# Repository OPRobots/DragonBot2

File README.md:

# DragonBot2

Robot **siguelíneas tipo Robotracer** de alto rendimiento para competir en la **All Japan Robotracer 2027**. Basado en un **STM32F405 @168 MHz**, con **24 sensores de línea** multiplexados, **tracción tetra** con 4 motores coreless, encoders magnéticos de alta resolución, **succión** y un **EKF de odometría** de 6 estados, todo con registro de datos a bordo y herramientas de análisis offline.

## 🎯 Objetivo

Desarrollar un robotracer competitivo para la **All Japan Robotracer 2027**. El firmware contempla tres modos de competición:

- **Linefollower**
- **Robotracer**
- **Drag race**

## 🏆 Palmarés

Todavía en desarrollo — **sin resultados de competición por el momento**.

| 🥇 | 🥈 | 🥉 |
| --- | --- | --- |
| **0** | **0** | **0** |

### Resultados por Evento

| Evento | Categoría | Posición | Año |
| --- | --- | --- | --- |
| _Pendiente_ | — | — | — |

---

## ⚙️ Hardware

- **Microcontrolador**: STM32F405RGT6 @168 MHz (LQFP-64)
- **Driver de motores**: 2× MP6615 (puente H con sensado de corriente bidireccional integrado)
- **IMU**: LSM6DSR (giroscopio, 1000/2000/4000 dps)
- **Encoders**: 2× AS5145B-HSST magnéticos de 12 bits (leídos en cuadratura ×4 por hardware → 4096 cuentas/vuelta)
- **Sensores de línea**: 24× ITR8307 (reflectivos) leídos a través de 3× multiplexores CD4051B
- **Sensores de marca**: 4× ITR8307 (laterales, para *landmarks* del robotracer)
- **Sensor de presión**: BMP280
- **Memoria externa**: SRAM SPI 23AA04M-I/ST de 512 KB + EEPROM en la flash interna del MCU
- **Receptor infrarrojo**: TSSP77038TR (38 kHz, mando RC5)
- **Regulador**: DC-DC conmutado CN3903 + LDO
- **Mosfet de succión**: BUK9Q20-40H
- **LEDs**: 1× LED RGB 5050, 10 LEDs de información, 1 LED de estado
- **Batería**: LiPo 3S (11,1–12,6 V), fabricada a partir de 3 celdas 1S de 300 mAh; conector JST-XH de 4 pines
- **Conectores de motores**: Hirose DF13 a 1,25 mm
- **Interfaz**: USB-C (ST-Link + USART3)

### Tracción

- **Tracción tetra**: 2 ruedas por lado, con **4 motores coreless de 7.4v** (2 por lado)
- **Reducción**: piñón de 8 dientes → engranaje de 40 dientes (**5:1**)
- **Ruedas**: Ø≈23 mm, con llanta impresa en PLA, una capa de espuma gruesa y una lámina de silicona exterior de gran adherencia
- **Succión**: doble ventilador centrífugo para aumentar el agarre a alta velocidad, usando **2 motores coreless de 7.4v**

### PCBs

El repositorio incluye dos placas diseñadas en KiCad (proyecto, gerbers y BOM):

- **Main**: MCU, drivers, sensores, encoders, memoria y regulación.
- **Chasis**: placa de chasis con pads de interconexión y switch de alimentación.

### Pinout (resumen)

| Función | Periférico / Pin |
| --- | --- |
| PWM motores | TIM1 CH1–CH4 (PA8–PA11) |
| Encoders | TIM3 (PB4/PB5), TIM4 (PB6/PB7) |
| Succión / RGB | TIM8 CH1–CH4 (PC6–PC9) |
| Sensores de línea | ADC1 IN10–IN12 (PC0–PC2) + selección de mux (PC13–PC15) |
| Sensores de marca / corriente de motor | ADC2 IN0–IN5 (PA0–PA5) |
| Tensión de batería | ADC2 IN13 (PC3) |
| IMU / BMP280 / SRAM | SPI3 (PC10–PC12) |
| Mando IR 38 kHz | EXTI12 (PA12) |
| Serie / ST-Link | USART3 (PB10/PB11) |

## 💻 Software

- Programado en **VSCode + PlatformIO** con **libopencm3**. Flasheo y depuración por **ST-Link**.
- **Scheduler** con **SysTick a 8 kHz** repartido en 8 slots → cada tarea corre a **1 kHz**.
- Todas las señales analógicas se leen por **DMA** (ADC1 y ADC2).
- Los **sensores de línea** se leen a través de los 3 multiplexores; la posición sobre la línea (rango ±1000) se calcula por media ponderada, con filtro de ventana **Bigger Filtro** y **detección automática del color de la línea** (blanca/negra).
- Los **encoders** se leen en **cuadratura por hardware** (TIM3/TIM4), con resolución de overflow por máxima verosimilitud.
- La **IMU** se lee por SPI con *data-ready*; el LSM6DSR se configura a ODR 833 Hz **sin filtro hardware** (medida cruda para el estimador).
- **Odometría con EKF de 6 estados** `[x, y, θ, v, ω, bias_gyro]`, con `dt` real medido por DWT, **ZUPT** y **detección de derrape**.
- **Lazo de control a 1 kHz** con PID de velocidad lineal y PID de posición de línea (angular) que reparte la tensión entre las ruedas, con **compensación de la tensión de batería**.
- **Estrategias de velocidad**: `SPEED_TEST`, `SPEED_NORMAL`, `SPEED_MEDIUM`, `SPEED_FAST`, `SPEED_SUPER` y `SPEED_HAKI` (2000–4000 mm/s), con ganancias escaladas ∝ 1/v.
- **Menú** de configuración y de *run* por LEDs, manejable con botones y con **mando RC5**; los parámetros se persisten en EEPROM.
- **Calibraciones**: offset del giroscopio, sensores, separación de ruedas (girando 2π con el gyro), escala de rueda (distancia patrón) y escalón de rotación (test T1).
- **Registro a bordo**: log en la **SRAM SPI de 512 KB** (ring en RAM + volcado diferido en los slots del SysTick), volcado por serie para análisis offline.

### Herramientas de análisis (`source_code/tools/`)

- `line_control_tuner.py` — métricas y predicción de ganancias del lazo de línea.
- `linear_speed_analyzer.py` — análisis del lazo de velocidad lineal y *feedforward*.
- `parse_odometry_log.py` — parseo y gráficas del log de odometría.

### Documentación técnica interna (`.features/`)

- `odometry/ROADMAP.md` — odometría y EKF.
- `pid_tuning/ROADMAP.md` — tuning del control de velocidad y de línea.
- `linear_speed/linear_speed_analysis_and_plan.md` — análisis del lazo lineal.

## 🎥 Vídeos

https://github.com/user-attachments/assets/3e48b05f-021b-4ee5-92f5-90e260f31eb7

## 📄 Licencia

Distribuido bajo la **PolyForm Noncommercial License 1.0.0**. Ver [LICENSE](LICENSE).

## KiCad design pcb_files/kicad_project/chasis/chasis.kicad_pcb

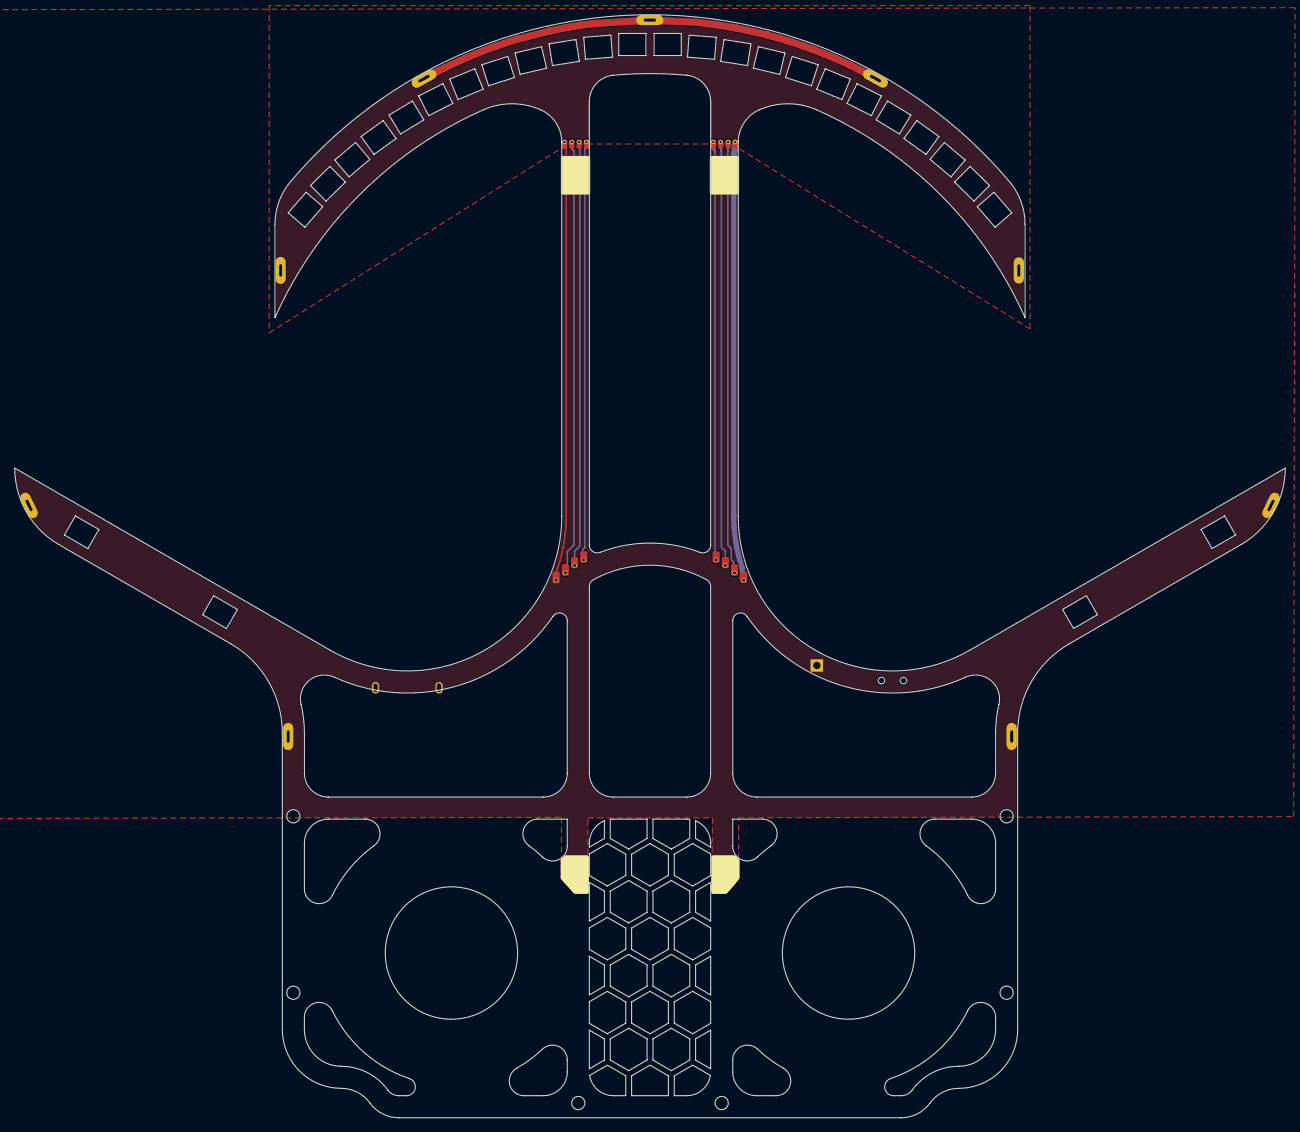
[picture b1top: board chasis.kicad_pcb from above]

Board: 2 copper layers, 172.8 x 150.0 mm, 6 parts (1 on the bottom side), 8 nets.

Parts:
J1: Conn_01x08_Pin; DragonBot_pads_main
J2: Conn_01x08_Pin; DragonBot_pads_morro
J3: Conn_01x01_Pin; PinHeader_1x01_P2.54mm_Vertical
JP2: SolderJumper_2_Open; SolderJumper-2_P1.3mm_Open_RoundedPad1.0x1.5mm
POWER_SWITCH1: SW_DPDT_x2; Generic_Swich_ONOFF
USB1: USB-C ST-Link USART

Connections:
GND: J1.1, J2.1, J3.1 (Pin_1_1), USB1.13 (SHIELD)
unnamed: J1.2, J2.2
unnamed: J1.3, J2.3
unnamed: J1.4, J2.4
unnamed: J1.5, J2.5
unnamed: J1.6, J2.6
unnamed: J1.7, J2.7
unnamed: J1.8, J2.8

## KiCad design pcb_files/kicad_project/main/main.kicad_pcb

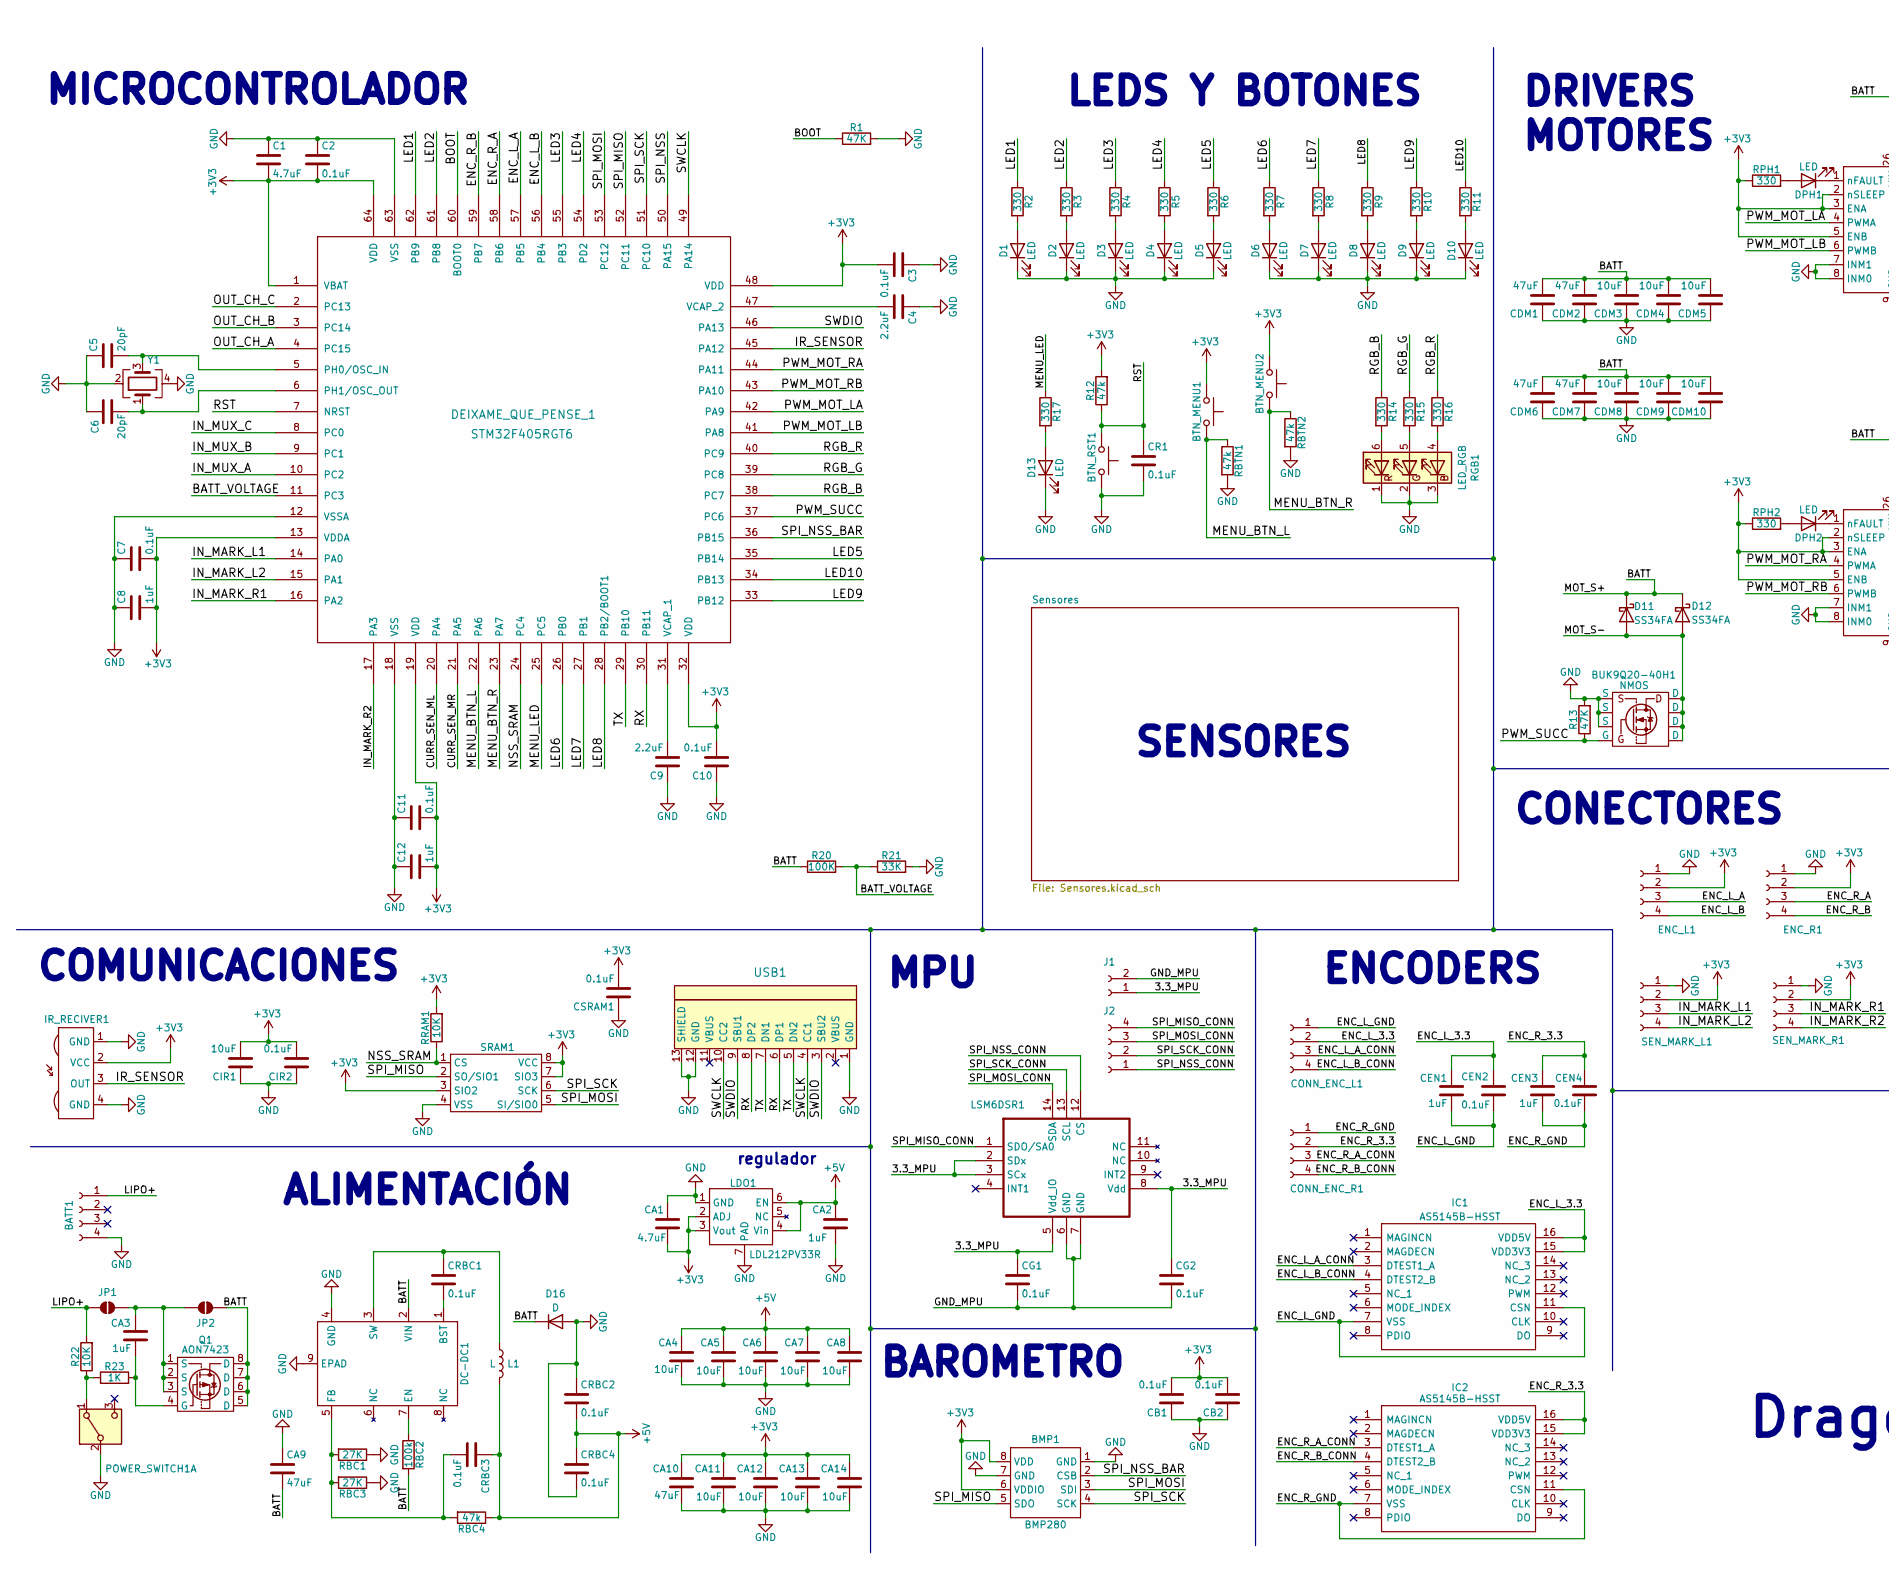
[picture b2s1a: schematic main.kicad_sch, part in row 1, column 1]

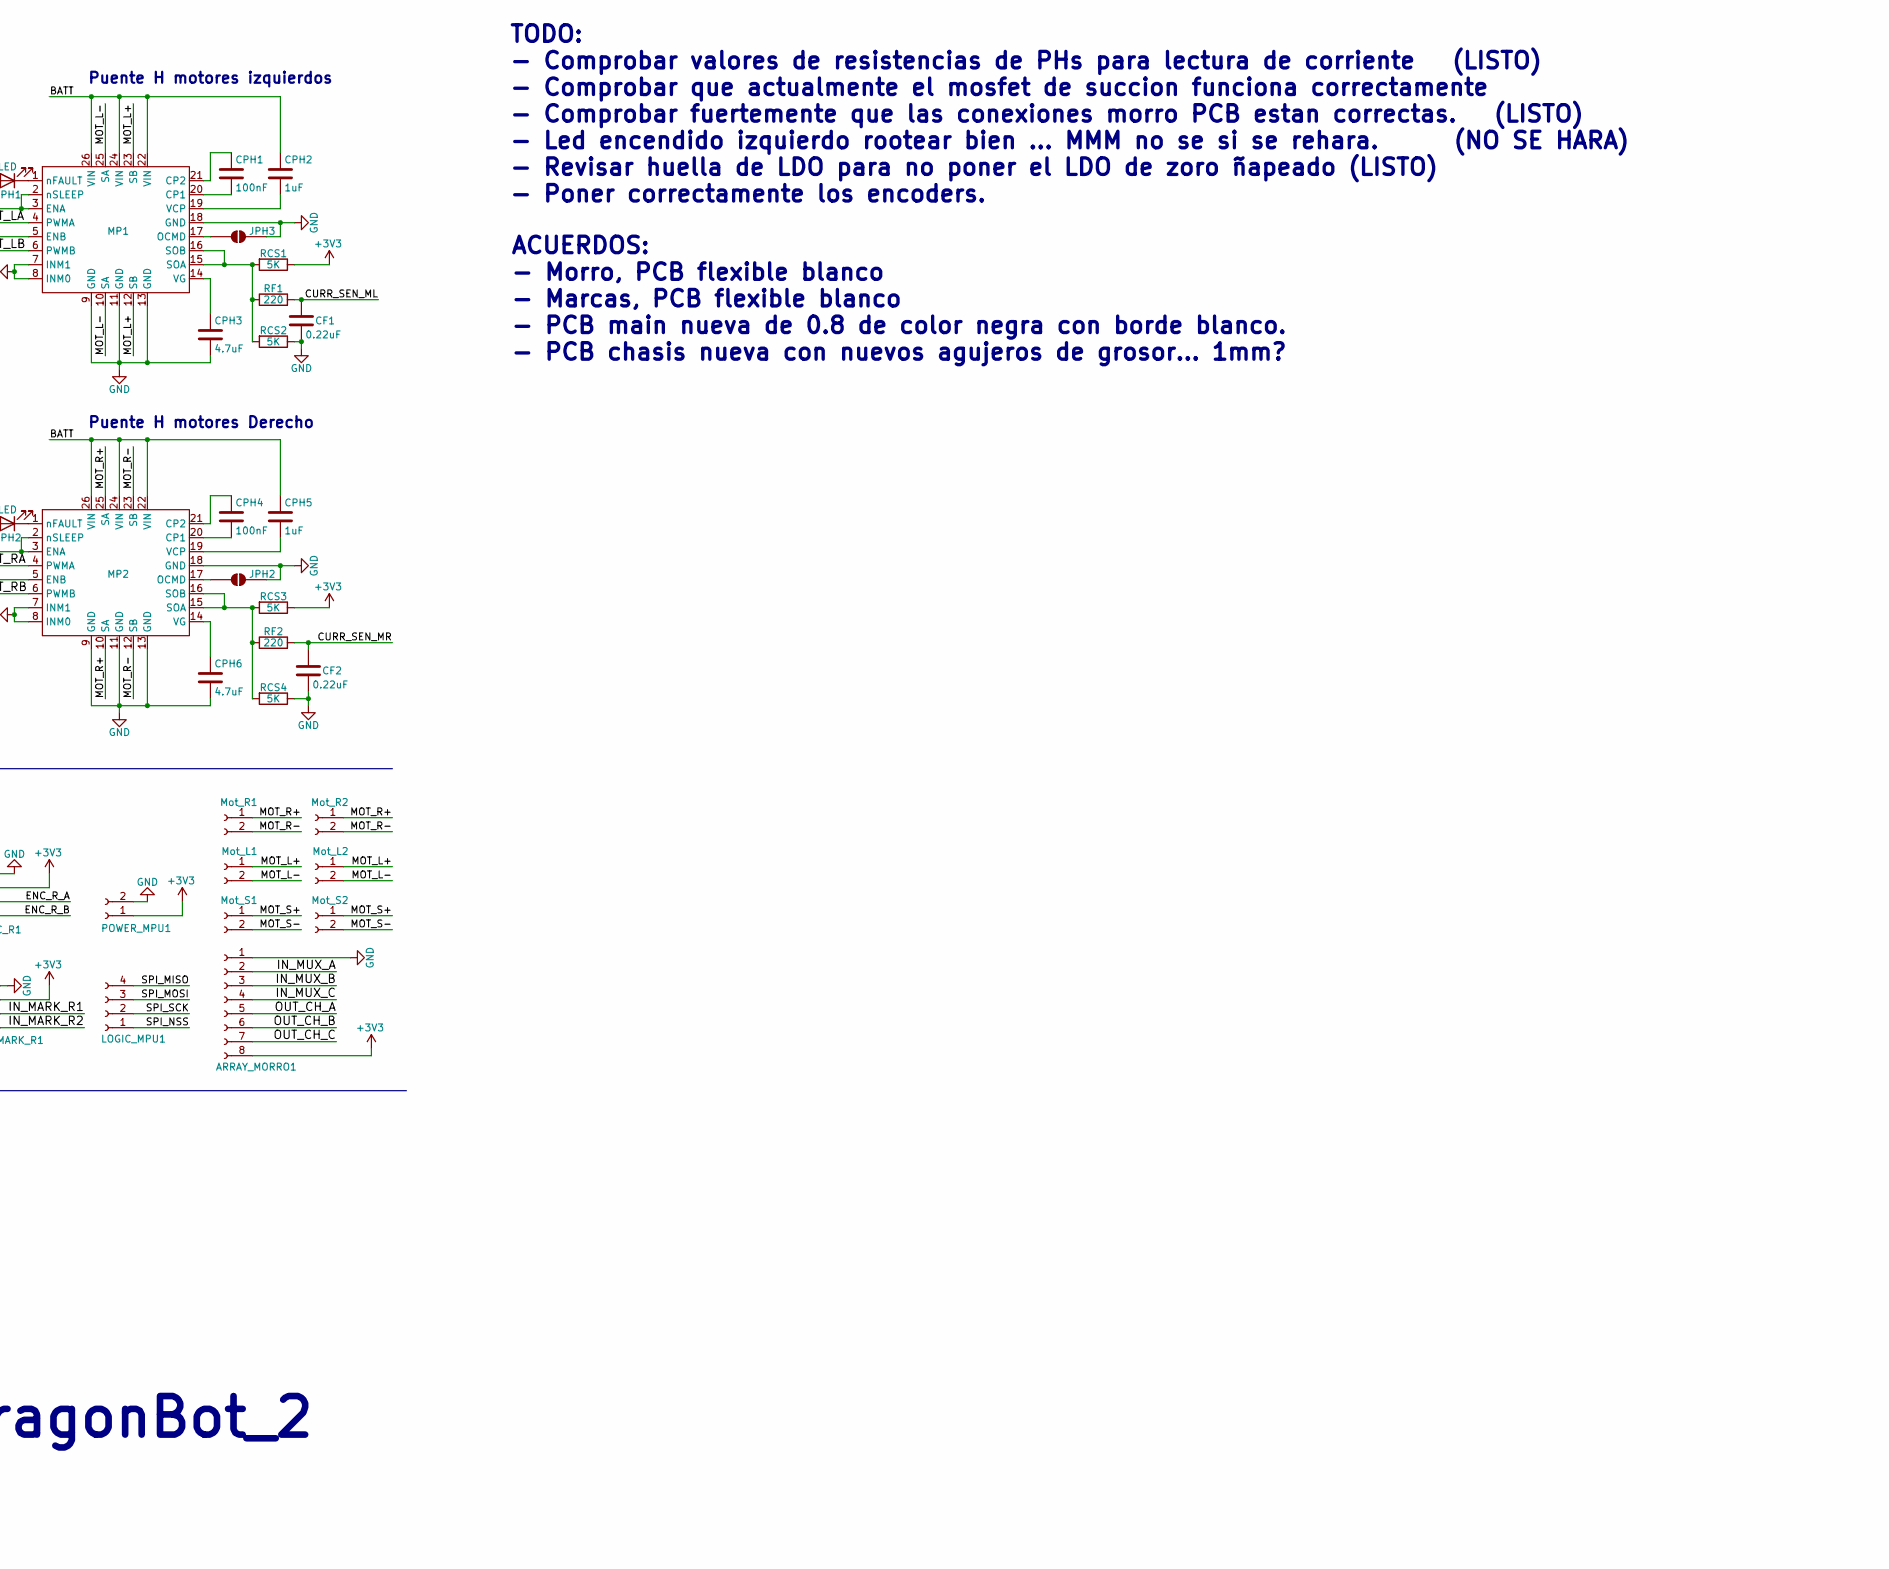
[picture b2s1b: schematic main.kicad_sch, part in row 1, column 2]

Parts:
ARRAY_MORRO1: Conn_01x08_Socket; DragonBot_pads_main
BATT1: Conn_01x04_Socket; JST_XH_B4B-XH-AM_1x04_P2.50mm_Vertical
BMP1: BMP280; Bosch_LGA-8_2.5x2.5mm_P0.65mm_ClockwisePinNumbering
BTN_MENU1, BTN_MENU2: Generic_SmallButton_6x3
BTN_RST1: Generic_SmallButton_6x3
BUK9Q20-40H1: NMOS; Mosfet_succion_BUK9Q20
C1: 4.7uF; C_0402_1005Metric_Pad0.74x0.62mm_HandSolder
C2, C3, C7, C10, C11: 0.1uF; C_0402_1005Metric_Pad0.74x0.62mm_HandSolder
C4, C9: 2.2uF; C_0402_1005Metric_Pad0.74x0.62mm_HandSolder
C5, C6: 20pF; C_0402_1005Metric_Pad0.74x0.62mm_HandSolder
C8, C12: 1uF; C_0402_1005Metric_Pad0.74x0.62mm_HandSolder
CA1: 4.7uF; C_0402_1005Metric_Pad0.74x0.62mm_HandSolder
CA2, CA3: 1uF; C_0402_1005Metric_Pad0.74x0.62mm_HandSolder
CA4, CA5, CA6, CA7, CA8, CA11, CA12, CA13, CA14: 10uF; C_0402_1005Metric_Pad0.74x0.62mm_HandSolder
CA9: 47uF; C_1206_3216Metric
CA10: 47uF; C_0805_2012Metric
CB1, CB2: 0.1uF; C_0402_1005Metric_Pad0.74x0.62mm_HandSolder
CDM1, CDM2, CDM6, CDM7: 47uF; C_0805_2012Metric
CDM3, CDM4, CDM5, CDM8, CDM9, CDM10: 10uF; C_0402_1005Metric_Pad0.74x0.62mm_HandSolder
CEN1, CEN3: 1uF; C_0402_1005Metric_Pad0.74x0.62mm_HandSolder
CEN2, CEN4: 0.1uF; C_0402_1005Metric_Pad0.74x0.62mm_HandSolder
CF1, CF2: 0.22uF; C_0402_1005Metric_Pad0.74x0.62mm_HandSolder
CG1, CG2: 0.1uF; C_0402_1005Metric_Pad0.74x0.62mm_HandSolder
CIR1: 10uF; C_0402_1005Metric_Pad0.74x0.62mm_HandSolder
CIR2: 0.1uF; C_0402_1005Metric_Pad0.74x0.62mm_HandSolder
CONN_ENC_L1: Conn_01x04_Socket; DragonBot_PCBmodule_encoder
CONN_ENC_R1: Conn_01x04_Socket; DragonBot_PCBmodule_encoder
CPH1, CPH4: 100nF; C_0402_1005Metric_Pad0.74x0.62mm_HandSolder
CPH2, CPH5: 1uF; C_0402_1005Metric_Pad0.74x0.62mm_HandSolder
CPH3, CPH6: 4.7uF; C_0402_1005Metric_Pad0.74x0.62mm_HandSolder
CR1: 0.1uF; C_0402_1005Metric_Pad0.74x0.62mm_HandSolder
CRBC1, CRBC2, CRBC3, CRBC4: 0.1uF; C_0402_1005Metric_Pad0.74x0.62mm_HandSolder
CSRAM1: 0.1uF; C_0402_1005Metric_Pad0.74x0.62mm_HandSolder
D1, D2, D3, D4, D5, D6, D7, D8, D9, D10: LED; LED_0805_2012Metric
D11, D12: SS34FA; D_SOD-123
D13: LED; LED_0402_1005Metric_Pad0.77x0.64mm_HandSolder
D16: D; D_0805_2012Metric_Pad1.15x1.40mm_HandSolder
DC-DC1: Texas_HTSOP-8-1EP_3.9x4.9mm_P1.27mm_EP2.95x4.9mm_Mask2.4x3.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
DEIXAME_QUE_PENSE_1: STM32F405RGT6; LQFP-64_10x10mm_P0.5mm
DPH1, DPH2: LED; LED_0402_1005Metric_Pad0.77x0.64mm_HandSolder
ENC_L1: Conn_01x04_Socket; DragonBot2_PCBmain_Encoder
ENC_R1: Conn_01x04_Socket; DragonBot2_PCBmain_Encoder
IC1, IC2: AS5145B-HSST; Encoder_AS5145B
IR_RECIVER1: IR_SENSOR_SMD_TSSP77038ETR
J1: Conn_01x02_Socket; ZoroBot3_Power_MPU
J2: Conn_01x04_Socket; ZoroBot3_Data_MPU
JP1, JP2: SolderJumper_2_Open; SolderJumper-2_P1.3mm_Open_RoundedPad1.0x1.5mm
JPH2, JPH3: JPH2; SolderJumper-2_P1.3mm_Open_RoundedPad1.0x1.5mm
L1: L; L_Wuerth_HCM-7050
LDO1: LDL212PV33R; DFN-6-2x2mm_P0.5mm_LDO_Dragonbot
LOGIC_MPU1: Conn_01x04_Socket; ZoroBot3_Data_MPU
LSM6DSR1: LGA-14_3x2.5mm_P0.5mm_LayoutBorder3x4y
MP1, MP2: MP6615
Mot_L1, Mot_L2: Conn_01x02_Socket; Connector_motor_1.25_Hirose_DF13-02P-1.25DSA_1x02_P1.25mm_V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
Mot_R1, Mot_R2: Conn_01x02_Socket; Connector_motor_1.25_Hirose_DF13-02P-1.25DSA_1x02_P1.25mm_V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
Mot_S1, Mot_S2: Conn_01x02_Socket; Connector_motor_1.25_Hirose_DF13-02P-1.25DSA_1x02_P1.25mm_V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
POWER_MPU1: Conn_01x02_Socket; ZoroBot3_Power_MPU
POWER_SWITCH1: SW_DPDT_x2; Generic_Swich_ONOFF
Q1: AON7423
R1, R13: 47K; R_0402_1005Metric_Pad0.72x0.64mm_HandSolder
R2, R3, R4, R5, R6, R7, R8, R9, R10, R11, R14, R15, R16, R17: 330; R_0402_1005Metric_Pad0.72x0.64mm_HandSolder
R12: 47k; R_0402_1005Metric_Pad0.72x0.64mm_HandSolder
R20: 100K; R_0402_1005Metric_Pad0.72x0.64mm_HandSolder
R21: 33K; R_0402_1005Metric_Pad0.72x0.64mm_HandSolder
R22: 10K; R_0402_1005Metric_Pad0.72x0.64mm_HandSolder
R23: 1K; R_0402_1005Metric_Pad0.72x0.64mm_HandSolder
RBC1, RBC3: 27K; R_0402_1005Metric_Pad0.72x0.64mm_HandSolder
RBC2: 100k; R_0402_1005Metric_Pad0.72x0.64mm_HandSolder
RBC4: 47k; R_0402_1005Metric_Pad0.72x0.64mm_HandSolder
RBTN1, RBTN2: 47k; R_0402_1005Metric_Pad0.72x0.64mm_HandSolder
RCS1, RCS2, RCS3, RCS4: 5K; R_0402_1005Metric_Pad0.72x0.64mm_HandSolder
RF1, RF2: 220; R_0402_1005Metric_Pad0.72x0.64mm_HandSolder
RGB1: LED_RGB; LED_RGB_5050-6
RPH1, RPH2: 330; R_0402_1005Metric_Pad0.72x0.64mm_HandSolder
RRAM1: 10K; R_0402_1005Metric_Pad0.72x0.64mm_HandSolder
SEN_MARK_L1: Conn_01x04_Socket; DragonBot_pad_marcas
SEN_MARK_R1: Conn_01x04_Socket; DragonBot_pad_marcas
SRAM1: 23AA04M-I/ST; TSSOP-8_4.4x3mm_P0.65mm
USB1: USB-C ST-Link USART
Y1: Crystal_GND24; Crystal_SMD_TXC_7M-4Pin_3.2x2.5mm

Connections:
+3V3: ARRAY_MORRO1.8, BMP1.6 (VDDIO), BMP1.8 (VDD), BTN_MENU1.1, BTN_MENU2.1, C1.2, C2.2, C3.2, C7.2, C8.2, C10.2, C11.2, C12.2, CA1.2, CA10.1, CA11.1, CA12.1, CA13.1, CA14.1, CB1.2, CB2.2, CIR1.2, CIR2.2, CSRAM1.2, DEIXAME_QUE_PENSE_1.1 (VBAT), DEIXAME_QUE_PENSE_1.13 (VDDA), DEIXAME_QUE_PENSE_1.19 (VDD), DEIXAME_QUE_PENSE_1.32 (VDD), DEIXAME_QUE_PENSE_1.48 (VDD), DEIXAME_QUE_PENSE_1.64 (VDD), ENC_L1.2, ENC_R1.2, IR_RECIVER1.2 (VCC), LDO1.2 (ADJ), LDO1.3 (Vout), MP1.2 (nSLEEP), MP1.3 (ENA), MP1.5 (ENB), MP2.2 (nSLEEP), MP2.3 (ENA), MP2.5 (ENB), POWER_MPU1.1, R12.2, RCS1.1, RCS3.1, RPH1.1, RPH2.1, RRAM1.2, SEN_MARK_L1.2, SEN_MARK_R1.2, SRAM1.3 (SIO2), SRAM1.7 (SIO3), SRAM1.8 (VCC)
+5V: CA2.1, CA4.1, CA5.1, CA6.1, CA7.1, CA8.1, CRBC2.2, CRBC3.1, CRBC4.1, L1.2, LDO1.4 (Vin), LDO1.6 (EN), RBC4.1
/3.3_MPU: CG1.1, CG2.1, J1.1, LSM6DSR1.2 (SDx), LSM6DSR1.3 (SCx), LSM6DSR1.5 (Vdd_IO), LSM6DSR1.8 (Vdd); also elsewhere on the board
/BATT: CA9.2, CDM1.2, CDM2.2, CDM3.2, CDM4.2, CDM5.2, CDM6.2, CDM7.2, CDM8.2, CDM9.2, CDM10.2, CPH2.1, CPH5.1, D11.1 (K), D12.1 (K), D16.1 (K), DC-DC1.2 (VIN), JP2.2 (B), MP1.22 (VIN), MP1.24 (VIN), MP1.26 (VIN), MP2.22 (VIN), MP2.24 (VIN), MP2.26 (VIN), Mot_S1.1, Mot_S2.1, Q1.5 (D), Q1.6 (D), Q1.7 (D), Q1.8 (D), R20.1, RBC2.2
/BATT_VOLTAGE: DEIXAME_QUE_PENSE_1.11 (PC3), R20.2, R21.1
/BOOT: DEIXAME_QUE_PENSE_1.60 (BOOT0), R1.1
/CURR_SEN_ML: CF1.1, DEIXAME_QUE_PENSE_1.20 (PA4), RF1.2
/CURR_SEN_MR: CF2.1, DEIXAME_QUE_PENSE_1.21 (PA5), RF2.2
/ENC_L_3.3: CEN1.1, CEN2.1, CONN_ENC_L1.2, IC1.15 (VDD3V3), IC1.16 (VDD5V)
/ENC_L_A: DEIXAME_QUE_PENSE_1.57 (PB5), ENC_L1.3
/ENC_L_A_CONN: CONN_ENC_L1.3, IC1.3 (DTEST1_A)
/ENC_L_B: DEIXAME_QUE_PENSE_1.56 (PB4), ENC_L1.4
/ENC_L_B_CONN: CONN_ENC_L1.4, IC1.4 (DTEST2_B)
/ENC_L_GND: CEN1.2, CEN2.2, CONN_ENC_L1.1, IC1.7 (VSS), IC1.11 (CSN)
/ENC_R_3.3: CEN3.1, CEN4.1, CONN_ENC_R1.2, IC2.15 (VDD3V3), IC2.16 (VDD5V)
/ENC_R_A: DEIXAME_QUE_PENSE_1.58 (PB6), ENC_R1.3
/ENC_R_A_CONN: CONN_ENC_R1.3, IC2.3 (DTEST1_A)
/ENC_R_B: DEIXAME_QUE_PENSE_1.59 (PB7), ENC_R1.4
/ENC_R_B_CONN: CONN_ENC_R1.4, IC2.4 (DTEST2_B)
/ENC_R_GND: CEN3.2, CEN4.2, CONN_ENC_R1.1, IC2.7 (VSS), IC2.11 (CSN)
/GND_MPU: CG1.2, CG2.2, J1.2, LSM6DSR1.6 (GND), LSM6DSR1.7 (GND)
/IN_MARK_L1: DEIXAME_QUE_PENSE_1.14 (PA0), SEN_MARK_L1.3
/IN_MARK_L2: DEIXAME_QUE_PENSE_1.15 (PA1), SEN_MARK_L1.4
/IN_MARK_R1: DEIXAME_QUE_PENSE_1.16 (PA2), SEN_MARK_R1.3
/IN_MARK_R2: DEIXAME_QUE_PENSE_1.17 (PA3), SEN_MARK_R1.4
/IN_MUX_A: ARRAY_MORRO1.2, DEIXAME_QUE_PENSE_1.10 (PC2)
/IN_MUX_B: ARRAY_MORRO1.3, DEIXAME_QUE_PENSE_1.9 (PC1)
/IN_MUX_C: ARRAY_MORRO1.4, DEIXAME_QUE_PENSE_1.8 (PC0)
/IR_SENSOR: DEIXAME_QUE_PENSE_1.45 (PA12), IR_RECIVER1.3 (OUT)
/LED1: DEIXAME_QUE_PENSE_1.62 (PB9), R2.1
/LED2: DEIXAME_QUE_PENSE_1.61 (PB8), R3.1
/LED3: DEIXAME_QUE_PENSE_1.55 (PB3), R4.1
/LED4: DEIXAME_QUE_PENSE_1.54 (PD2), R5.1
/LED5: DEIXAME_QUE_PENSE_1.35 (PB14), R6.1
/LED6: DEIXAME_QUE_PENSE_1.26 (PB0), R7.1
/LED7: DEIXAME_QUE_PENSE_1.27 (PB1), R8.1
/LED8: DEIXAME_QUE_PENSE_1.28 (PB2/BOOT1), R9.1
/LED9: DEIXAME_QUE_PENSE_1.33 (PB12), R10.1
/LED10: DEIXAME_QUE_PENSE_1.34 (PB13), R11.1
/LIPO+: BATT1.1, JP1.2 (B), R22.2
/MENU_BTN_L: BTN_MENU1.2, DEIXAME_QUE_PENSE_1.22 (PA6), RBTN1.1
/MENU_BTN_R: BTN_MENU2.2, DEIXAME_QUE_PENSE_1.23 (PA7), RBTN2.1
/MENU_LED: DEIXAME_QUE_PENSE_1.25 (PC5), R17.1
/MOT_L+: MP1.12 (SB), MP1.23 (SB), Mot_L1.1, Mot_L2.1
/MOT_L-: MP1.10 (SA), MP1.25 (SA), Mot_L1.2, Mot_L2.2
/MOT_R+: MP2.10 (SA), MP2.25 (SA), Mot_R1.1, Mot_R2.1
/MOT_R-: MP2.12 (SB), MP2.23 (SB), Mot_R1.2, Mot_R2.2
/MOT_S-: BUK9Q20-40H1.5 (D), BUK9Q20-40H1.6 (D), BUK9Q20-40H1.7 (D), BUK9Q20-40H1.8 (D), D11.2 (A), D12.2 (A), Mot_S1.2, Mot_S2.2
/NSS_SRAM: DEIXAME_QUE_PENSE_1.24 (PC4), RRAM1.1, SRAM1.1 (CS)
/OUT_CH_A: ARRAY_MORRO1.5, DEIXAME_QUE_PENSE_1.4 (PC15)
/OUT_CH_B: ARRAY_MORRO1.6, DEIXAME_QUE_PENSE_1.3 (PC14)
/OUT_CH_C: ARRAY_MORRO1.7, DEIXAME_QUE_PENSE_1.2 (PC13)
/PWM_MOT_LA: DEIXAME_QUE_PENSE_1.42 (PA9), MP1.4 (PWMA)
/PWM_MOT_LB: DEIXAME_QUE_PENSE_1.41 (PA8), MP1.6 (PWMB)
/PWM_MOT_RA: DEIXAME_QUE_PENSE_1.44 (PA11), MP2.4 (PWMA)
/PWM_MOT_RB: DEIXAME_QUE_PENSE_1.43 (PA10), MP2.6 (PWMB)
/PWM_SUCC: BUK9Q20-40H1.4 (G), DEIXAME_QUE_PENSE_1.37 (PC6), R13.1
/RGB_B: DEIXAME_QUE_PENSE_1.38 (PC7), R14.1
/RGB_G: DEIXAME_QUE_PENSE_1.39 (PC8), R15.1
/RGB_R: DEIXAME_QUE_PENSE_1.40 (PC9), R16.1
/RST: BTN_RST1.1, CR1.1, DEIXAME_QUE_PENSE_1.7 (NRST), R12.1
/RX: DEIXAME_QUE_PENSE_1.30 (PB11), USB1.6 (DP1), USB1.8 (DP2)
/SPI_MISO: BMP1.5 (SDO), DEIXAME_QUE_PENSE_1.52 (PC11), LOGIC_MPU1.4, SRAM1.2 (SO/SIO1)
/SPI_MISO_CONN: J2.4, LSM6DSR1.1 (SDO/SA0)
/SPI_MOSI: BMP1.3 (SDI), DEIXAME_QUE_PENSE_1.53 (PC12), LOGIC_MPU1.3, SRAM1.5 (SI/SIO0)
/SPI_MOSI_CONN: J2.3, LSM6DSR1.14 (SDA)
/SPI_NSS: DEIXAME_QUE_PENSE_1.50 (PA15), LOGIC_MPU1.1
/SPI_NSS_BAR: BMP1.2 (CSB), DEIXAME_QUE_PENSE_1.36 (PB15)
/SPI_NSS_CONN: J2.1, LSM6DSR1.12 (CS)
/SPI_SCK: BMP1.4 (SCK), DEIXAME_QUE_PENSE_1.51 (PC10), LOGIC_MPU1.2, SRAM1.6 (SCK)
/SPI_SCK_CONN: J2.2, LSM6DSR1.13 (SCL)
/SWCLK: DEIXAME_QUE_PENSE_1.49 (PA14), USB1.4 (CC1), USB1.10 (CC2)
/SWDIO: DEIXAME_QUE_PENSE_1.46 (PA13), USB1.3 (SBU2), USB1.9 (SBU1)
/TX: DEIXAME_QUE_PENSE_1.29 (PB10), USB1.5 (DN2), USB1.7 (DN1)
GND: ARRAY_MORRO1.1, BATT1.4, BMP1.1 (GND), BMP1.7 (GND), BTN_RST1.2, BUK9Q20-40H1.1 (S), BUK9Q20-40H1.2 (S), BUK9Q20-40H1.3 (S), C1.1, C2.1, C3.1, C4.1, C5.1, C6.1, C7.1, C8.1, C9.1, C10.1, C11.1, C12.1, CA1.1, CA2.2, CA4.2, CA5.2, CA6.2, CA7.2, CA8.2, CA9.1, CA10.2, CA11.2, CA12.2, CA13.2, CA14.2, CB1.1, CB2.1, CDM1.1, CDM2.1, CDM3.1, CDM4.1, CDM5.1, CDM6.1, CDM7.1, CDM8.1, CDM9.1, CDM10.1, CF1.2, CF2.2, CIR1.1, CIR2.1, CPH3.2, CPH6.2, CR1.2, CRBC2.1, CRBC4.2, CSRAM1.1, D1.1 (K), D2.1 (K), D3.1 (K), D4.1 (K), D5.1 (K), D6.1 (K), D7.1 (K), D8.1 (K), D9.1 (K), D10.1 (K), D13.1 (K), D16.2 (A), DC-DC1.4 (GND), DC-DC1.9 (EPAD), DEIXAME_QUE_PENSE_1.12 (VSSA), DEIXAME_QUE_PENSE_1.18 (VSS), DEIXAME_QUE_PENSE_1.63 (VSS), ENC_L1.1, ENC_R1.1, IR_RECIVER1.1 (GND), IR_RECIVER1.4 (GND), JPH2.2 (B), JPH3.2 (B), LDO1.1 (GND), LDO1.7 (PAD), MP1.7 (INM1), MP1.8 (INM0), MP1.9 (GND), MP1.11 (GND), MP1.13 (GND), MP1.18 (GND), MP2.7 (INM1), MP2.8 (INM0), MP2.9 (GND), MP2.11 (GND), MP2.13 (GND), MP2.18 (GND), POWER_MPU1.2, POWER_SWITCH1.2 (B), R1.2, R13.2, R21.2, RBC1.1, RBC3.1, RBTN1.2, RBTN2.2, RCS2.1, RCS4.1, RGB1.1 (RK), RGB1.2 (GK), RGB1.3 (BK), SEN_MARK_L1.1, SEN_MARK_R1.1, SRAM1.4 (VSS), USB1.1 (GND), USB1.12 (GND), USB1.13 (SHIELD), Y1.2, Y1.4
unnamed: D1.2 (A), R2.2
unnamed: D2.2 (A), R3.2
unnamed: D3.2 (A), R4.2
unnamed: D4.2 (A), R5.2
unnamed: D5.2 (A), R6.2
unnamed: D6.2 (A), R7.2
unnamed: D7.2 (A), R8.2
unnamed: D8.2 (A), R9.2
unnamed: D9.2 (A), R10.2
unnamed: D10.2 (A), R11.2
unnamed: D13.2 (A), R17.2
unnamed: CRBC1.2, DC-DC1.1 (BST)
unnamed: DC-DC1.7 (EN), RBC2.1
unnamed: CRBC3.2, DC-DC1.5 (FB), RBC1.2, RBC3.2, RBC4.2
unnamed: CRBC1.1, DC-DC1.3 (SW), L1.1
unnamed: C5.2, DEIXAME_QUE_PENSE_1.5 (PH0/OSC_IN), Y1.3
unnamed: C6.2, DEIXAME_QUE_PENSE_1.6 (PH1/OSC_OUT), Y1.1
unnamed: C9.2, DEIXAME_QUE_PENSE_1.31 (VCAP_1)
unnamed: C4.2, DEIXAME_QUE_PENSE_1.47 (VCAP_2)
unnamed: DPH1.2 (A), RPH1.2
unnamed: DPH1.1 (K), MP1.1 (nFAULT)
unnamed: DPH2.2 (A), RPH2.2
unnamed: DPH2.1 (K), MP2.1 (nFAULT)
unnamed: CA3.1, JP1.1 (A), JP2.1 (A), Q1.1 (S), Q1.2 (S), Q1.3 (S)
unnamed: JPH2.1 (A), MP2.17 (OCMD)
unnamed: JPH3.1 (A), MP1.17 (OCMD)
unnamed: CPH1.2, MP1.20 (CP1)
unnamed: CPH1.1, MP1.21 (CP2)
unnamed: MP1.15 (SOA), MP1.16 (SOB), RCS1.2, RCS2.2, RF1.1
unnamed: CPH2.2, MP1.19 (VCP)
unnamed: CPH3.1, MP1.14 (VG)
unnamed: CPH4.2, MP2.20 (CP1)
unnamed: CPH4.1, MP2.21 (CP2)
unnamed: MP2.15 (SOA), MP2.16 (SOB), RCS3.2, RCS4.2, RF2.1
unnamed: CPH5.2, MP2.19 (VCP)
unnamed: CPH6.1, MP2.14 (VG)
unnamed: POWER_SWITCH1.1 (A), R22.1, R23.1
unnamed: CA3.2, Q1.4 (G), R23.2
unnamed: R16.2, RGB1.4 (BA)
unnamed: R15.2, RGB1.5 (GA)
unnamed: R14.2, RGB1.6 (RA)

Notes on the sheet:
MICROCONTROLADOR
BAROMETRO
DRIVERS MOTORES
DragonBot_2
Puente H motores Derecho
TODO: - Comprobar valores de resistencias de PHs para lectura de corriente (LISTO) - Comprobar que actualmente el mosfet de succion funciona correctamente - Comprobar fuertemente que las conexiones morro PCB estan correctas. (LISTO) - Led encendido izquierdo rootear bien ... MMM no se si se rehara.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
Puente H motores izquierdos
LEDS Y BOTONES
regulador
ENCODERS
CONECTORES
MPU
SENSORES
ALIMENTACIÓN
ACUERDOS: - Morro, PCB flexible blanco - Marcas, PCB flexible blanco - PCB main nueva de 0.8 de color negra con borde blanco. - PCB chasis nueva con nuevos agujeros de grosor... 1mm?
COMUNICACIONES

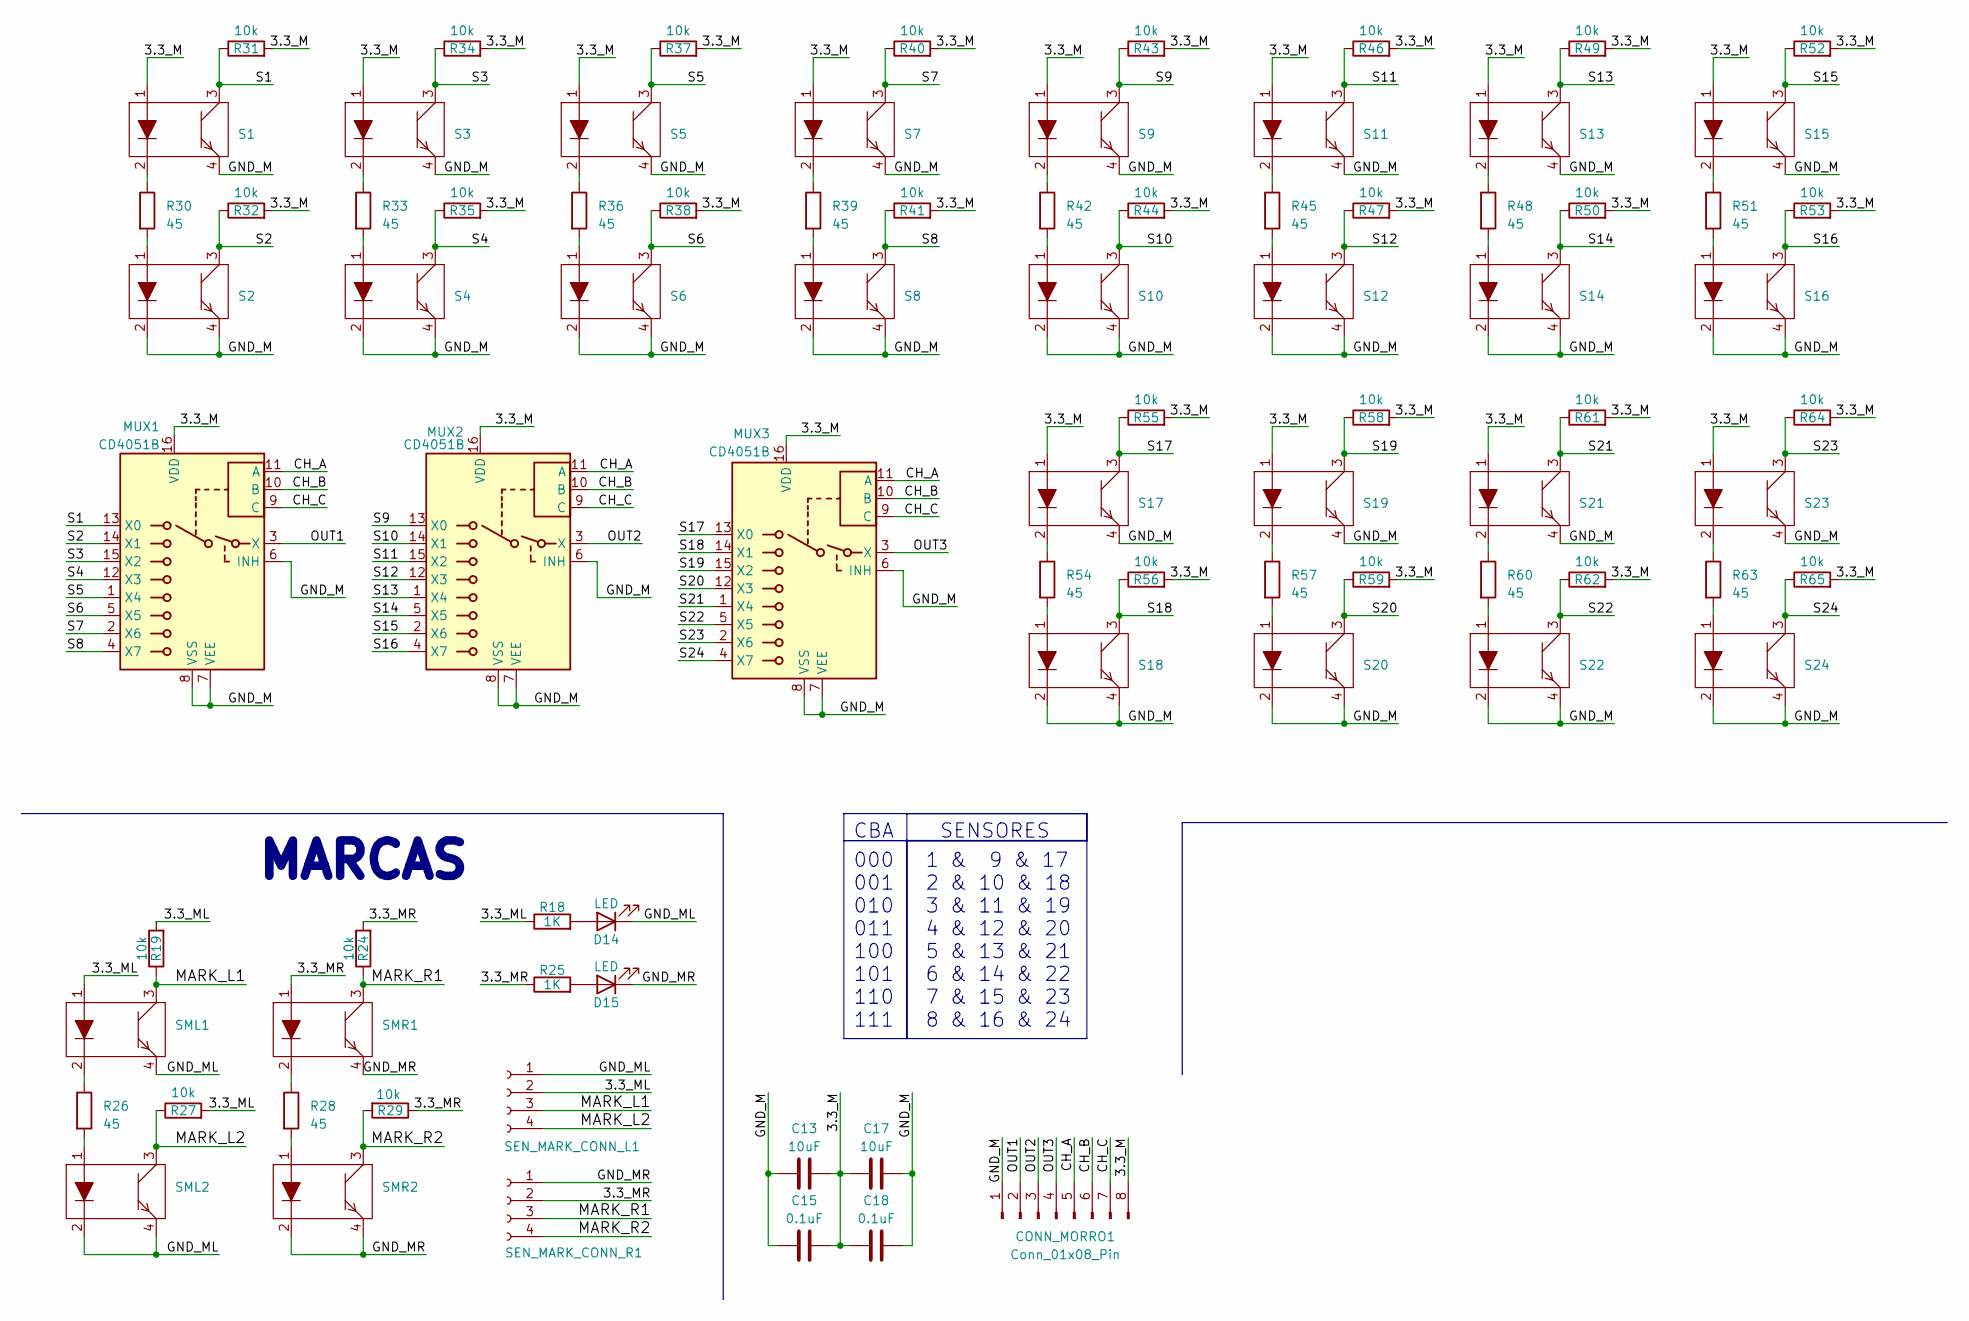
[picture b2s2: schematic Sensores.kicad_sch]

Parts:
C13, C17: 10uF; C_0805_2012Metric_Pad1.18x1.45mm_HandSolder; LCSC Part # C380331
C15, C18: 0.1uF; C_0805_2012Metric_Pad1.18x1.45mm_HandSolder; LCSC Part # C2847428
CONN_MORRO1: Conn_01x08_Pin; DragonBot_pads_morro
D14, D15: LED; LED_0402_1005Metric_Pad0.77x0.64mm_HandSolder
MUX1, MUX2, MUX3: CD4051B; MUX_CD4051B; LCSC Part # C3007951
R18, R25: 1K; R_0402_1005Metric_Pad0.72x0.64mm_HandSolder
R19, R24, R27, R29, R31, R32, R34, R35, R37, R38, R40, R41, R43, R44, R46, R47, R49, R50, R52, R53, R55, R56, R58, R59, R61, R62, R64, R65: 10k; R_0402_1005Metric_Pad0.72x0.64mm_HandSolder; LCSC Part # C17414
R26, R28, R30, R33, R36, R39, R42, R45, R48, R51, R54, R57, R60, R63: 45; R_0402_1005Metric_Pad0.72x0.64mm_HandSolder; LCSC Part # C3017827
S1, S2, S3, S4, S5, S6, S7, S8, S9, S10, S11, S12, S13, S14, S15, S16, S17, S18, S19, S20, S21, S22, S23, S24: DragonBot2_QRE1113; LCSC Part # C81632
SEN_MARK_CONN_L1: Conn_01x04_Socket; DragonBot_pad_marcas
SEN_MARK_CONN_R1: Conn_01x04_Socket; DragonBot_pad_marcas
SML1, SML2: FujitoraBot2_QRE1113; LCSC Part # C81632
SMR1, SMR2: FujitoraBot2_QRE1113; LCSC Part # C81632

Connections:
/Sensores/3.3_M: C13.1, C15.1, C17.2, C18.2, CONN_MORRO1.8, MUX1.16 (VDD), MUX2.16 (VDD), MUX3.16 (VDD), R31.2, R32.2, R34.2, R35.2, R37.2, R38.2, R40.2, R41.2, R43.2, R44.2, R46.2, R47.2, R49.2, R50.2, R52.2, R53.2, R55.2, R56.2, R58.2, R59.2, R61.2, R62.2, R64.2, R65.2, S1.1, S3.1, S5.1, S7.1, S9.1, S11.1, S13.1, S15.1, S17.1, S19.1, S21.1, S23.1
/Sensores/3.3_ML: R18.1, R19.2, R27.2, SEN_MARK_CONN_L1.2, SML1.1
/Sensores/3.3_MR: R24.2, R25.1, R29.1, SEN_MARK_CONN_R1.2, SMR1.1
/Sensores/CH_A: CONN_MORRO1.5, MUX1.11 (A), MUX2.11 (A), MUX3.11 (A)
/Sensores/CH_B: CONN_MORRO1.6, MUX1.10 (B), MUX2.10 (B), MUX3.10 (B)
/Sensores/CH_C: CONN_MORRO1.7, MUX1.9 (C), MUX2.9 (C), MUX3.9 (C)
/Sensores/GND_M: C13.2, C15.2, C17.1, C18.1, CONN_MORRO1.1, MUX1.6 (INH), MUX1.7 (VEE), MUX1.8 (VSS), MUX2.6 (INH), MUX2.7 (VEE), MUX2.8 (VSS), MUX3.6 (INH), MUX3.7 (VEE), MUX3.8 (VSS), S1.4, S2.2, S2.4, S3.4, S4.2, S4.4, S5.4, S6.2, S6.4, S7.4, S8.2, S8.4, S9.4, S10.2, S10.4, S11.4, S12.2, S12.4, S13.4, S14.2, S14.4, S15.4, S16.2, S16.4, S17.4, S18.2, S18.4, S19.4, S20.2, S20.4, S21.4, S22.2, S22.4, S23.4, S24.2, S24.4
/Sensores/GND_ML: D14.1 (K), SEN_MARK_CONN_L1.1, SML1.4, SML2.2, SML2.4
/Sensores/GND_MR: D15.1 (K), SEN_MARK_CONN_R1.1, SMR1.4, SMR2.2, SMR2.4
/Sensores/MARK_L1: R19.1, SEN_MARK_CONN_L1.3, SML1.3
/Sensores/MARK_L2: R27.1, SEN_MARK_CONN_L1.4, SML2.3
/Sensores/MARK_R1: R24.1, SEN_MARK_CONN_R1.3, SMR1.3
/Sensores/MARK_R2: R29.2, SEN_MARK_CONN_R1.4, SMR2.3
/Sensores/OUT1: CONN_MORRO1.2, MUX1.3 (X)
/Sensores/OUT2: CONN_MORRO1.3, MUX2.3 (X)
/Sensores/OUT3: CONN_MORRO1.4, MUX3.3 (X)
/Sensores/S1: MUX1.13 (X0), R31.1, S1.3
/Sensores/S2: MUX1.14 (X1), R32.1, S2.3
/Sensores/S3: MUX1.15 (X2), R34.1, S3.3
/Sensores/S4: MUX1.12 (X3), R35.1, S4.3
/Sensores/S5: MUX1.1 (X4), R37.1, S5.3
/Sensores/S6: MUX1.5 (X5), R38.1, S6.3
/Sensores/S7: MUX1.2 (X6), R40.1, S7.3
/Sensores/S8: MUX1.4 (X7), R41.1, S8.3
/Sensores/S9: MUX2.13 (X0), R43.1, S9.3
/Sensores/S10: MUX2.14 (X1), R44.1, S10.3
/Sensores/S11: MUX2.15 (X2), R46.1, S11.3
/Sensores/S12: MUX2.12 (X3), R47.1, S12.3
/Sensores/S13: MUX2.1 (X4), R49.1, S13.3
/Sensores/S14: MUX2.5 (X5), R50.1, S14.3
/Sensores/S15: MUX2.2 (X6), R52.1, S15.3
/Sensores/S16: MUX2.4 (X7), R53.1, S16.3
/Sensores/S17: MUX3.13 (X0), R55.1, S17.3
/Sensores/S18: MUX3.14 (X1), R56.1, S18.3
/Sensores/S19: MUX3.15 (X2), R58.1, S19.3
/Sensores/S20: MUX3.12 (X3), R59.1, S20.3
/Sensores/S21: MUX3.1 (X4), R61.1, S21.3
/Sensores/S22: MUX3.5 (X5), R62.1, S22.3
/Sensores/S23: MUX3.2 (X6), R64.1, S23.3
/Sensores/S24: MUX3.4 (X7), R65.1, S24.3
unnamed: D14.2 (A), R18.2
unnamed: D15.2 (A), R25.2
unnamed: R26.1, SML1.2
unnamed: R26.2, SML2.1
unnamed: R28.1, SMR1.2
unnamed: R28.2, SMR2.1
unnamed: R30.1, S1.2
unnamed: R30.2, S2.1
unnamed: R33.1, S3.2
unnamed: R33.2, S4.1
unnamed: R36.1, S5.2
unnamed: R36.2, S6.1
unnamed: R39.1, S7.2
unnamed: R39.2, S8.1
unnamed: R42.1, S9.2
unnamed: R42.2, S10.1
unnamed: R45.1, S11.2
unnamed: R45.2, S12.1
unnamed: R48.1, S13.2
unnamed: R48.2, S14.1
unnamed: R51.1, S15.2
unnamed: R51.2, S16.1
unnamed: R54.1, S17.2
unnamed: R54.2, S18.1
unnamed: R57.1, S19.2
unnamed: R57.2, S20.1
unnamed: R60.1, S21.2
unnamed: R60.2, S22.1
unnamed: R63.1, S23.2
unnamed: R63.2, S24.1

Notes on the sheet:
MARCAS
CBA
000 001 010 011 100 101 110 111
1 & 9 & 17 2 & 10 & 18 3 & 11 & 19 4 & 12 & 20 5 & 13 & 21 6 & 14 & 22 7 & 15 & 23 8 & 16 & 24
SENSORES
